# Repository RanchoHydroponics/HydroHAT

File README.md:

HydroHAT
========

The HydroHAT is an Arduino-based extension to the RPi Model B+. It controls sensors and actuators over I2C and takes care of control loops and lower-level logic, while using the RPi to run the user interface, via a touchscreen and a web interface.

In our case, it is being developed and used to control a hydroponics system, however, it should function well as a general controller for automation via RPi.

Additionally, the UART TX and RX from the RPi are passed through to a 4D Systems header for use with a 4D Systems touchscreen.

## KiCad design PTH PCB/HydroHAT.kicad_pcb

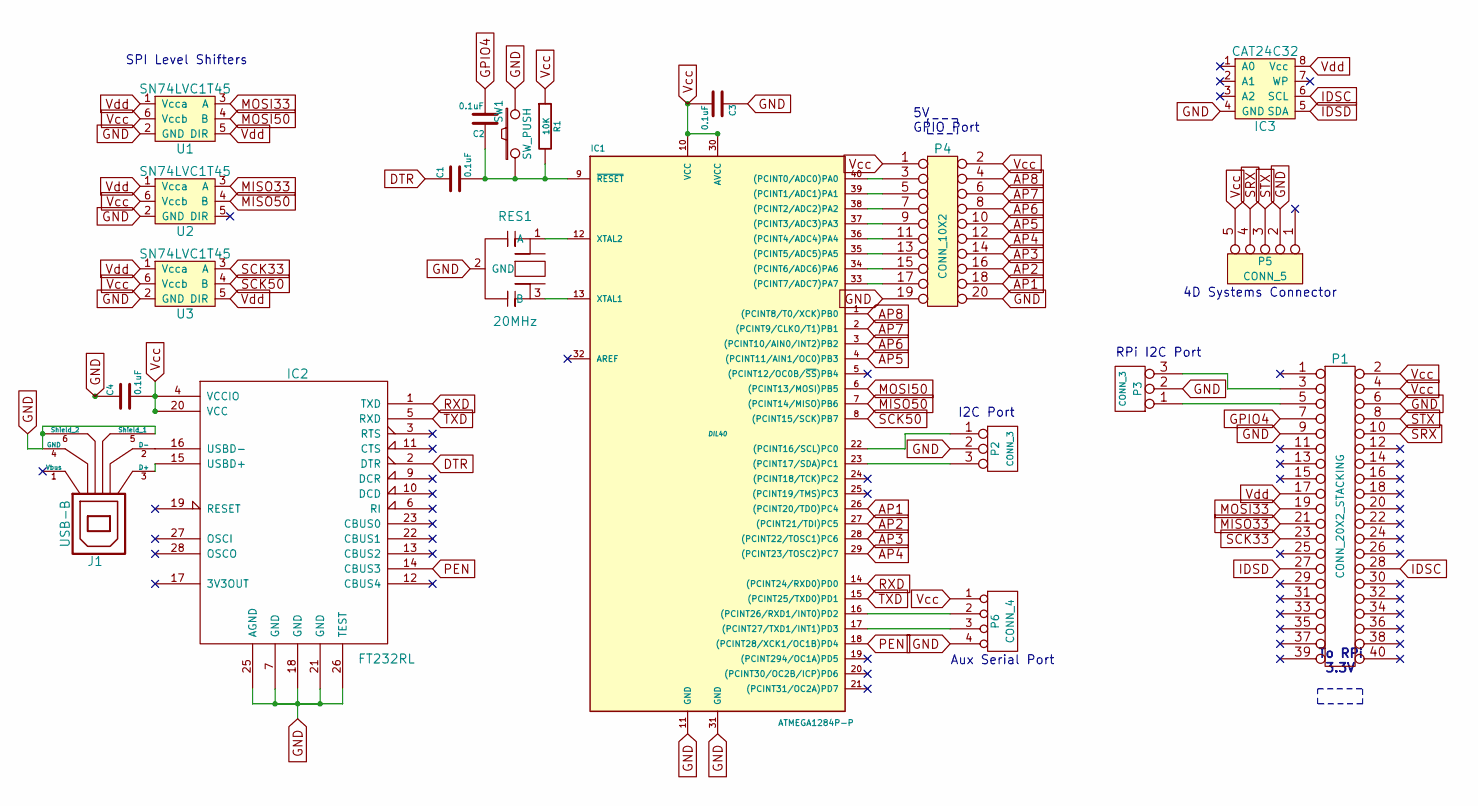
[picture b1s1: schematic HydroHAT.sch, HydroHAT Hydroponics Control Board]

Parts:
C1, C2, C3, C4: 0.1uF; MFG Part Num SR295E104MAR
IC1: ATMEGA1284P-P; DIL40; MFG Part Num ATMEGA1284P-PU
IC2: FT232RL; MFG Part Num FT232RL-TUBE
IC3: CAT24C32; MFG Part Num CAT24C32LI-G
J1: USB-B; MFG Part Num M701-330442
P1: CONN_20X2_STACKING; MFG Part Num M20-6102045
P2, P3: CONN_3; MFG Part Num 640456-3
P4: CONN_10X2; MFG Part Num 67996-420HLF
P5: CONN_5; MFG Part Num 640456-5
P6: CONN_4; MFG Part Num 640456-4
R1: 10K; MFG Part Num CF14JT10K0
RES1: 20MHz; MFG Part Num CSTLS20M0X53-B0
SW1: SW_PUSH; MFG Part Num 1825910-6
U1, U2, U3: SN74LVC1T45; MFG Part Num SN74LVC1T45DBVR

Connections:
AP1: IC1.26 ((PCINT20/TDO)PC4), P4.18
AP2: IC1.27 ((PCINT21/TDI)PC5), P4.16
AP3: IC1.28 ((PCINT22/TOSC1)PC6), P4.14
AP4: IC1.29 ((PCINT23/TOSC2)PC7), P4.12
AP5: IC1.4 ((PCINT11/AIN1/OC0)PB3), P4.10
AP6: IC1.3 ((PCINT10/AIN0/INT2)PB2), P4.8
AP7: IC1.2 ((PCINT9/CLKO/T1)PB1), P4.6
AP8: IC1.1 ((PCINT8/T0/XCK)PB0), P4.4
DTR: C1.1, IC2.2 (DTR)
GND: C3.1, C4.1, IC1.11 (GND), IC1.31 (GND), IC2.7 (GND), IC2.18 (GND), IC2.21 (GND), IC2.25 (AGND), IC2.26 (TEST), IC3.4 (GND), J1.4 (GND), J1.5 (Shield_1), J1.6 (Shield_2), P1.6, P1.9, P2.2 (PM), P3.2 (PM), P4.19, P4.20, P5.2, P6.4, RES1.2 (GND), SW1.2, U1.2 (GND), U2.2 (GND), U3.2 (GND)
GPIO4: C2.2, P1.7
IDSC: IC3.6 (SCL), P1.28
IDSD: IC3.5 (SDA), P1.27
MISO33: P1.21, U2.3 (A)
MISO50: IC1.7 ((PCINT14/MISO)PB6), U2.4 (B)
MOSI33: P1.19, U1.3 (A)
MOSI50: IC1.6 ((PCINT13/MOSI)PB5), U1.4 (B)
unnamed: P1.5, P3.1
unnamed: IC1.23 ((PCINT17/SDA)PC1), P2.3
unnamed: IC1.17 ((PCINT27/TXD1/INT1)PD3), P6.3
unnamed: IC1.16 ((PCINT26/RXD1/INT0)PD2), P6.2
unnamed: IC1.13 (XTAL1), RES1.3 (B)
unnamed: IC1.12 (XTAL2), RES1.1 (A)
unnamed: IC1.33 ((PCINT7/ADC7)PA7), P4.17
unnamed: IC2.15 (USBD+), J1.3 (D+)
unnamed: IC2.16 (USBD-), J1.2 (D-)
unnamed: IC1.22 ((PCINT16/SCL)PC0), P2.1
unnamed: P1.3, P3.3
unnamed: IC1.40 ((PCINT0/ADC0)PA0), P4.3
unnamed: IC1.39 ((PCINT1/ADC1)PA1), P4.5
unnamed: IC1.38 ((PCINT2/ADC2)PA2), P4.7
unnamed: IC1.37 ((PCINT3/ADC3)PA3), P4.9
unnamed: IC1.36 ((PCINT4/ADC4)PA4), P4.11
unnamed: IC1.35 ((PCINT5/ADC5)PA5), P4.13
unnamed: IC1.34 ((PCINT6/ADC6)PA6), P4.15
unnamed: C1.2, C2.1, IC1.9 (~RESET), R1.2, SW1.1
PEN: IC1.18 ((PCINT28/XCK1/OC1B)PD4), IC2.14 (CBUS3)
RXD: IC1.14 ((PCINT24/RXD0)PD0), IC2.1 (TXD)
SCK33: P1.23, U3.3 (A)
SCK50: IC1.8 ((PCINT15/SCK)PB7), U3.4 (B)
SRX: P1.10, P5.4
STX: P1.8, P5.3
TXD: IC1.15 ((PCINT25/TXD0)PD1), IC2.5 (RXD)
Vcc: C3.2, C4.2, IC1.10 (VCC), IC1.30 (AVCC), IC2.4 (VCCIO), IC2.20 (VCC), P1.2, P1.4, P4.1, P4.2, P5.5, P6.1, R1.1, U1.6 (Vccb), U2.6 (Vccb), U3.6 (Vccb)
Vdd: IC3.8 (Vcc), P1.17, U1.1 (Vcca), U1.5 (DIR), U2.1 (Vcca), U3.1 (Vcca), U3.5 (DIR)

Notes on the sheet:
To RPi 3.3V
Aux Serial Port
5V GPIO Port
I2C Port
RPi I2C Port
SPI Level Shifters
4D Systems Connector

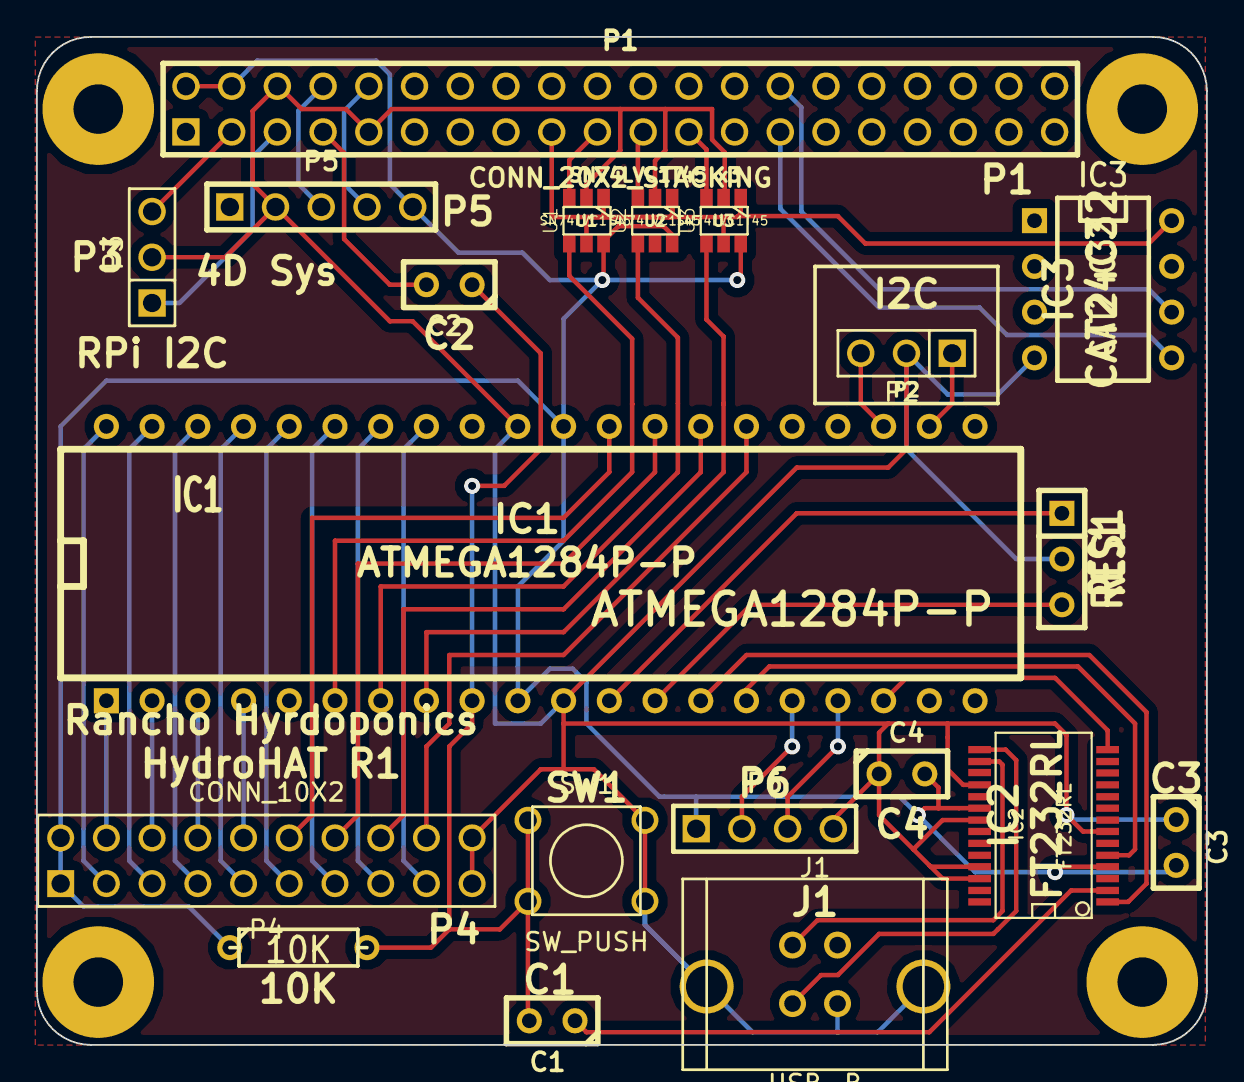
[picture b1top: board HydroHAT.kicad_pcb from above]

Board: 2 copper layers, 65.0 x 56.0 mm, 24 parts (0 on the bottom side), 45 nets.

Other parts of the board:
HAT-Hole: VAL**; HAT-Hole
HAT-Hole#2, HAT-Hole#3, HAT-Hole#4: VAL**; HAT-Hole

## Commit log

2014-09-19 Updated Readme
    And added KiCad project
2014-09-22 PCB Edges
2014-09-23 Schematic start
    And mostly done, still need to add FTDI
2014-09-23 Changed Things
    Stuff
2014-09-23 Added level shifting to schematic
2014-09-23 Started USB circuitry
2014-09-24 Almost done
    Just need to add two datasheets
2014-09-25 Schematic Done
    Working on footprints
2014-09-26 PTH PCB Complete
    Schematic also somewhat reworked.
2014-09-26 Updated Schematic PDF
    Whoops
2014-09-26 Added BOM And rejiggled some stuff
2014-10-11 Added stencil stuff
    Yep
